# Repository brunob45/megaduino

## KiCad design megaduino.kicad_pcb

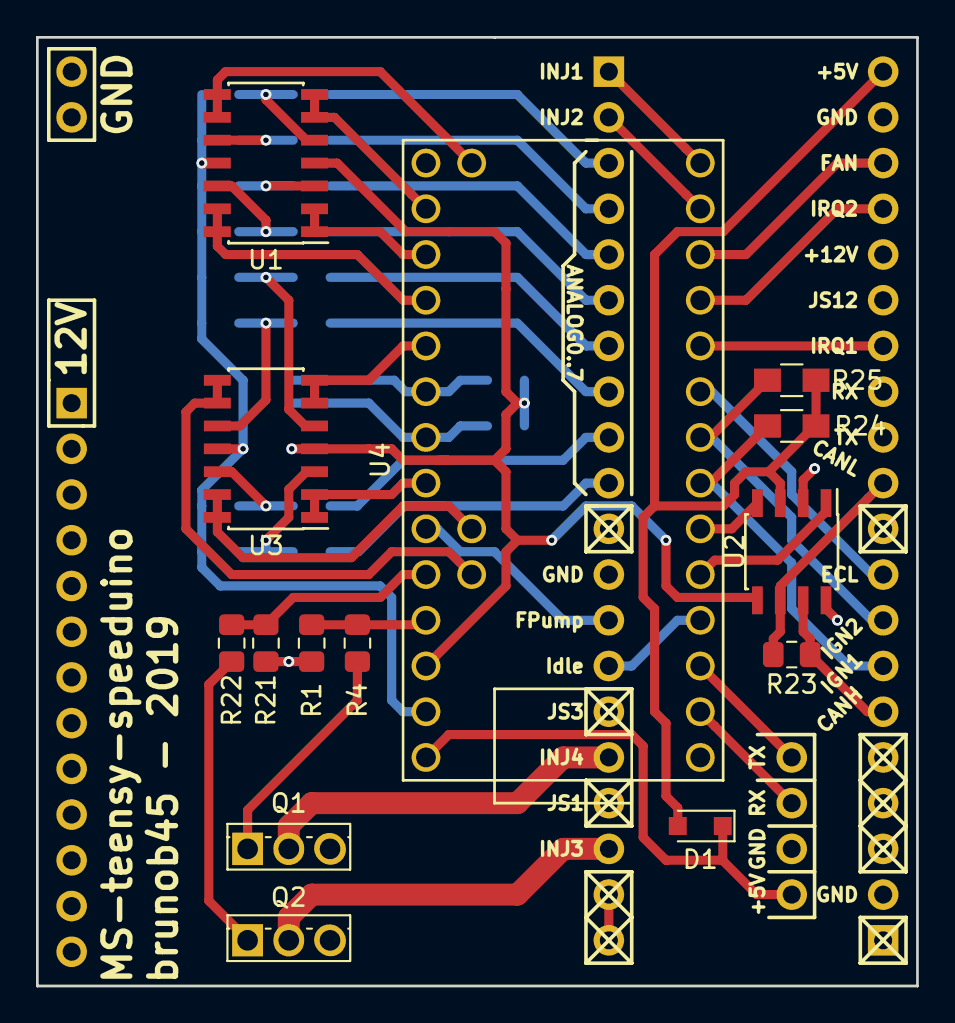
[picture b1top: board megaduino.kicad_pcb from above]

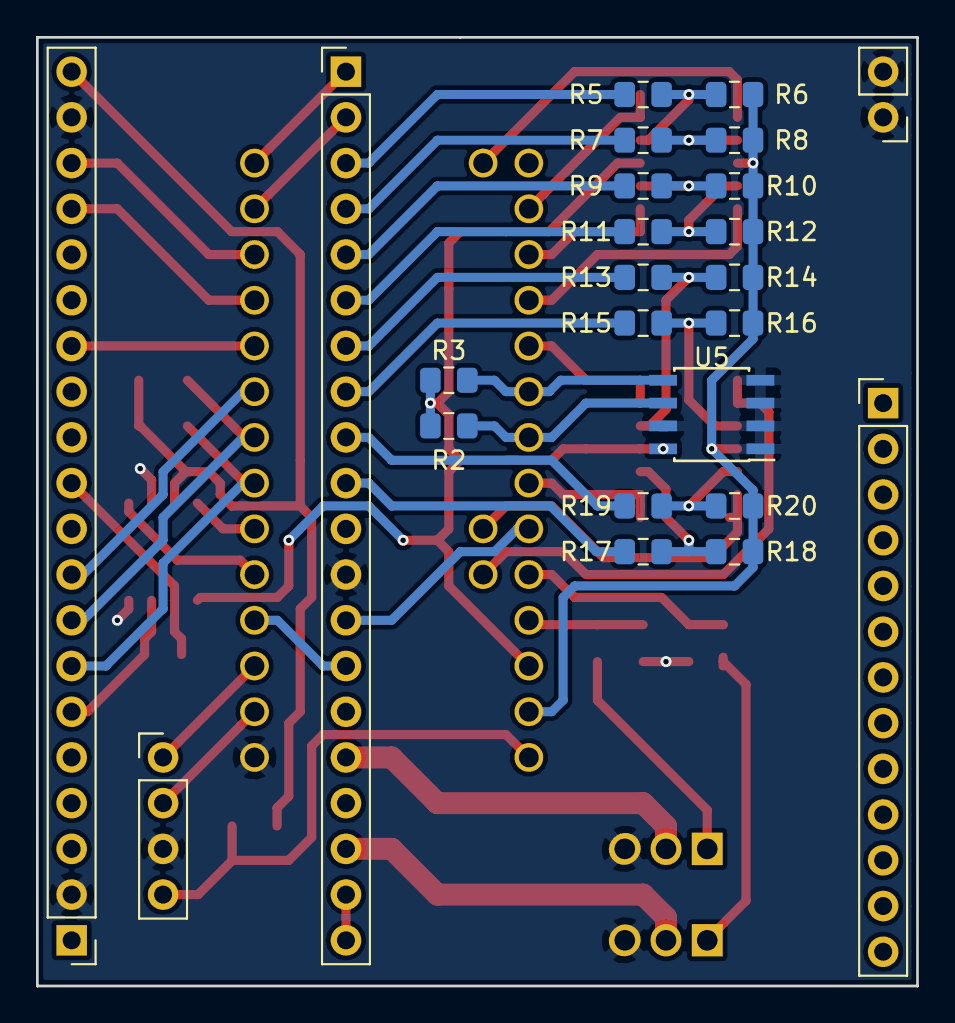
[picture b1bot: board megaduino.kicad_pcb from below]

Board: 2 copper layers, 48.9 x 52.7 mm, 38 parts (24 on the bottom side), 54 nets.

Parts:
D1: D_Schottky; D_SOD-323_HandSoldering
J1, J2: Conn_01x20_Female; Pin_Header_Straight_1x20_Pitch2.54mm
J3: Conn_01x13_Male; PinHeader_1x13_P2.54mm_Vertical
J4: Conn_01x02_Male; PinHeader_1x02_P2.54mm_Vertical
J5: Conn_01x04_Male; PinHeader_1x04_P2.54mm_Vertical
Q1, Q2: RFD14N05L; TO-251-3_Vertical
R1, R6, R8, R10, R12, R14, R16, R18, R20, R21: 91k; R_0805_2012Metric_Pad1.15x1.40mm_HandSolder
R2, R3, R4, R22: 1k; R_0805_2012Metric_Pad1.15x1.40mm_HandSolder
R5, R7, R9, R11, R13, R15, R17, R19: 49k; R_0805_2012Metric_Pad1.15x1.40mm_HandSolder
R23: 120; R_0805_2012Metric_Pad1.15x1.40mm_HandSolder
R24, R25: 1k; R_0805_HandSoldering
U1, U3: LMV324; SOIC-14_3.9x8.7mm_P1.27mm
U2: MCP2562-E-SN; SOIC-8_3.9x4.9mm_P1.27mm
U4: Teensy3.2; Teensy32
U5: AT24CS02-XHM; SOIC-8_3.9x4.9mm_P1.27mm

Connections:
+3V3: R2.1, R3.1, U1.4, U2.5, U3.4, U4.31, U5.8
+5V: D1.2, J1.20, R24.1, R25.1, U2.3
A0: U1.6, U1.7, U4.21
A1: U1.1, U1.2, U4.22
A2: U1.8, U1.9, U4.19
A3: U1.13, U1.14, U4.23
A4: U3.6, U3.7, U4.24
A5: U3.8, U3.9, U4.36
A6: U3.13, U3.14, U4.37
A7: U3.1, U3.2, U4.27
AD0: J2.3, R5.1
AD1: J2.4, R7.1
AD2: J2.5, R9.1
AD3: J2.6, R11.1
AD4: J2.7, R13.1
AD5: J2.8, R15.1
AD6: J2.9, R19.1
AD7: J2.10, R17.1
CANH: J1.6, R23.1, U2.7
CANL: J1.11, R23.2, U2.6
ECL: J1.9, U4.9
Earth: J1.2, J1.19, J2.12, J4.1, J4.2, J5.3, Q1.3, Q2.3, R1.1, R21.1, U2.2, U2.8, U4.1, U5.1, U5.2, U5.3, U5.4, U5.7
FAN: J1.18, U4.12
FP: J2.13, U4.28
GNDA: R6.2, R8.2, R10.2, R12.2, R14.2, R16.2, R18.2, R20.2, U1.11, U3.11, U4.32
IGN1: J1.7, R24.2, U4.7
IGN2: J1.8, R25.2, U4.8
INJ1: J2.1, U4.14
INJ2: J2.2, U4.13
INJ3: R21.2, R22.2, U4.29
INJ4: R1.2, R4.2, U4.30
IRQ0: J1.14, U4.10
IRQ1: J1.17, U4.11
Idle: J2.14, U4.4
JS0: J2.18, Q2.2
JS2: J2.16, Q1.2
unnamed: D1.1, J5.4, U4.33
unnamed: J2.19, J2.20
unnamed: J5.1, U4.3
unnamed: J5.2, U4.2
unnamed: Q1.1, R4.1
unnamed: Q2.1, R22.1
unnamed: R2.2, U4.26, U5.6
unnamed: R3.2, U4.25, U5.5
unnamed: R5.2, R6.1, U1.5
unnamed: R7.2, R8.1, U1.10
unnamed: R9.2, R10.1, U1.3
unnamed: R11.2, R12.1, U1.12
unnamed: R13.2, R14.1, U3.5
unnamed: R15.2, R16.1, U3.10
unnamed: R17.2, R18.1, U3.3
unnamed: R19.2, R20.1, U3.12
unnamed: U2.1, U4.5
unnamed: U2.4, U4.6

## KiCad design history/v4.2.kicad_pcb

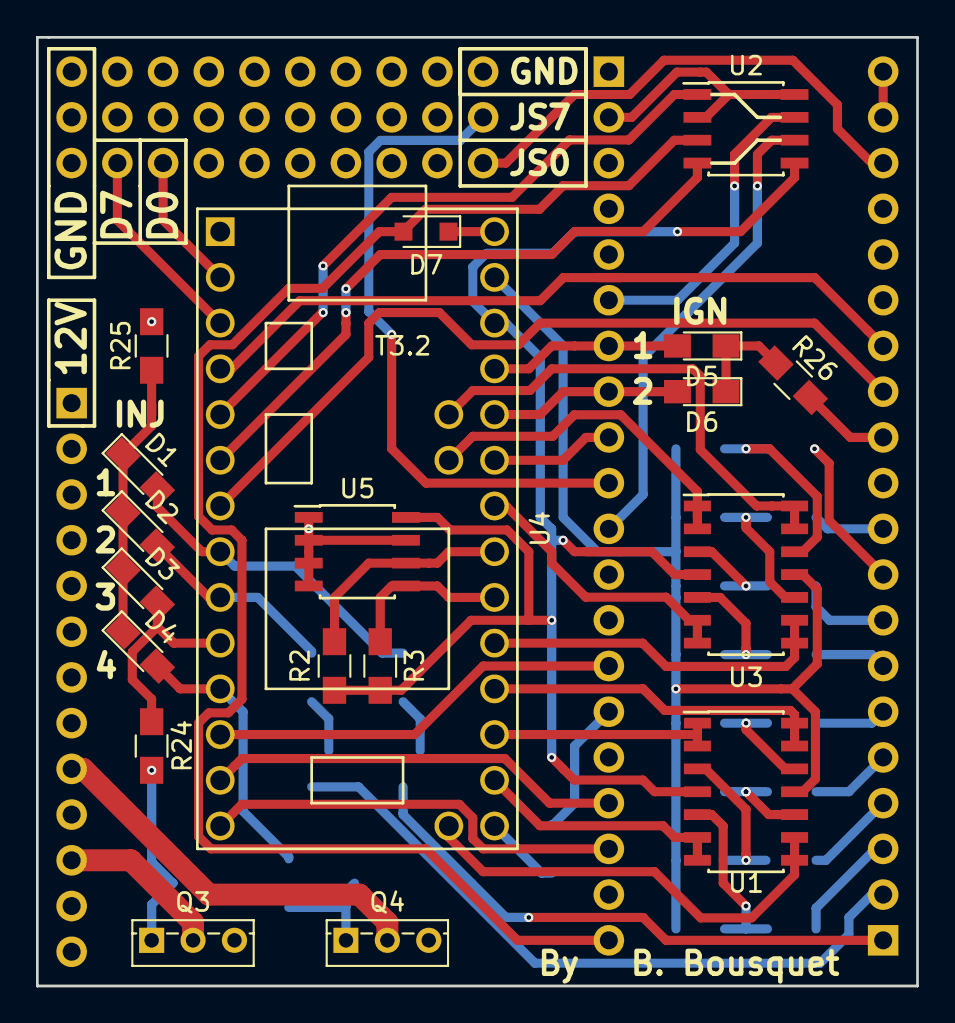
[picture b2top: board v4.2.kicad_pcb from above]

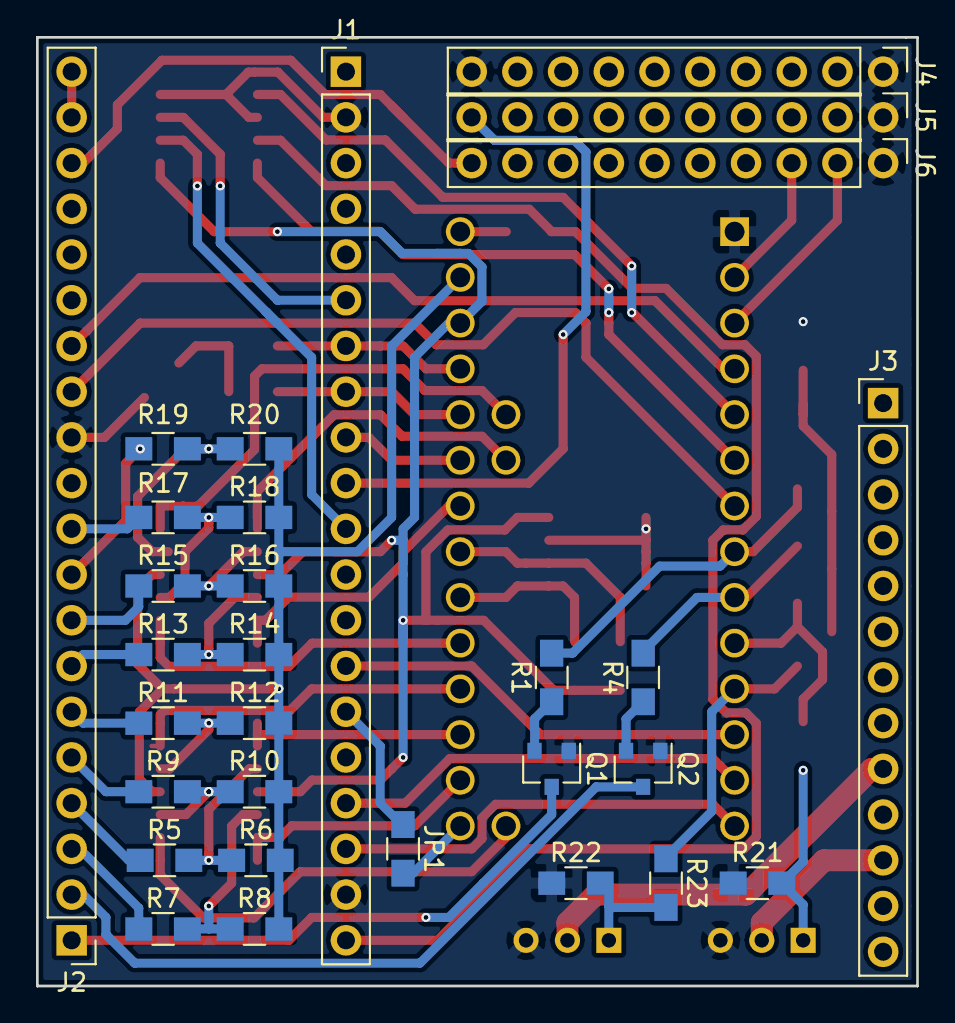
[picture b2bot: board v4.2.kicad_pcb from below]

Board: 2 copper layers, 48.9 x 52.7 mm, 49 parts (30 on the bottom side), 64 nets.

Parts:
D1, D2, D3, D4, D5, D6: LED; LED_0805_HandSoldering
D7: D_Schottky; D_SOD-323_HandSoldering
J1, J2: Conn_01x20_Female; Pin_Header_Straight_1x20_Pitch2.54mm
J3: Conn_01x13_Male; Pin_Header_Straight_1x13_Pitch2.54mm
J4, J5, J6: Conn_01x10_Male; Pin_Header_Straight_1x10_Pitch2.54mm
JP1: Jumper; R_0805_HandSoldering
Q1, Q2: 2N2219; SOT-23
Q3, Q4: Q_NMOS_GDS; TO-251_IPAK_Vertical
R1, R2, R3, R4, R23, R24: 1k; R_0805_HandSoldering
R5, R7, R9, R11, R13, R15, R17, R19: 180k; R_0805_HandSoldering
R6, R8, R10, R12, R14, R16, R18, R20: 330k; R_0805_HandSoldering
R21, R22: 100k; R_0805_HandSoldering
R25, R26: R; R_0805_HandSoldering
U1, U3: LMV324; SOIC-14_3.9x8.7mm_Pitch1.27mm
U2: MCP2562-E/P; SOIC-8_3.9x4.9mm_Pitch1.27mm
U4: Teensy3.2; Teensy32
U5: AT24CS02-XHM; SOIC-8_3.9x4.9mm_Pitch1.27mm

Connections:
+3V3: R2.1, R3.1, U1.4, U2.5, U3.4, U4.31, U5.8
+5V: D7.2, J1.20, U2.3
A0: U1.6, U1.7, U4.21
A1: U1.1, U1.2, U4.22
A2: U1.8, U1.9, U4.19
A3: U1.13, U1.14, U4.23
A4: U3.6, U3.7, U4.27
A5: U3.1, U3.2, U4.37
A6: U3.13, U3.14, U4.36
A7: U3.8, U3.9, U4.24
AD0: J2.3, R7.1
AD1: J2.4, R5.1
AD2: J2.5, R9.1
AD3: J2.6, R11.1
AD4: J2.7, R13.1
AD5: J2.8, R15.1
AD6: J2.9, R19.1
AD7: J2.10, R17.1
CANH: J1.6, U2.7
CANL: J1.11, U2.6
D0: J6.3, U4.2
D7: J6.2, U4.3
ECL: J1.9, U4.28
Earth: J1.2, J1.19, J2.12, J4.1, J4.10, J5.1, J6.1, Q1.1, Q2.1, Q3.3, Q4.3, R21.1, R22.1, R25.2, R26.2, U2.2, U2.8, U4.1, U5.1, U5.2, U5.3, U5.4, U5.7
FAN: J1.18, U4.14
FP: J2.13, U4.7
GNDA: R6.2, R8.2, R10.2, R12.2, R14.2, R16.2, R18.2, R20.2, U1.11, U3.11, U4.32
IGN1: D5.2, J1.7, U4.30
IGN2: D6.2, J1.8, U4.29
INJ1: D1.2, R1.2, U4.8
INJ2: D2.2, R4.2, U4.9
INJ3: D3.2, R24.1, U4.10
INJ4: D4.2, R23.1, U4.11
IRQ0: J1.14, U4.12
IRQ1: J1.17, U4.13
Idle: J2.14, U4.4
JS0: J2.18, J6.10
JS7: J1.10, J5.10
JS12: J1.15, JP1.1
unnamed: D1.1, D2.1, D3.1, D4.1, R25.1
unnamed: D5.1, D6.1, R26.1
unnamed: D7.1, U4.33
unnamed: J2.1, Q1.3
unnamed: J2.2, Q2.3
unnamed: J2.19, J2.20
unnamed: J3.9, Q4.2
unnamed: J3.11, Q3.2
unnamed: JP1.2, U4.20
unnamed: Q1.2, R1.1
unnamed: Q2.2, R4.1
unnamed: Q3.1, R21.2, R24.2
unnamed: Q4.1, R22.2, R23.2
unnamed: R2.2, U4.26, U5.6
unnamed: R3.2, U4.25, U5.5
unnamed: R5.2, R6.1, U1.3
unnamed: R7.2, R8.1, U1.5
unnamed: R9.2, R10.1, U1.10
unnamed: R11.2, R12.1, U1.12
unnamed: R13.2, R14.1, U3.5
unnamed: R15.2, R16.1, U3.3
unnamed: R17.2, R18.1, U3.10
unnamed: R19.2, R20.1, U3.12
unnamed: U2.1, U4.5
unnamed: U2.4, U4.6

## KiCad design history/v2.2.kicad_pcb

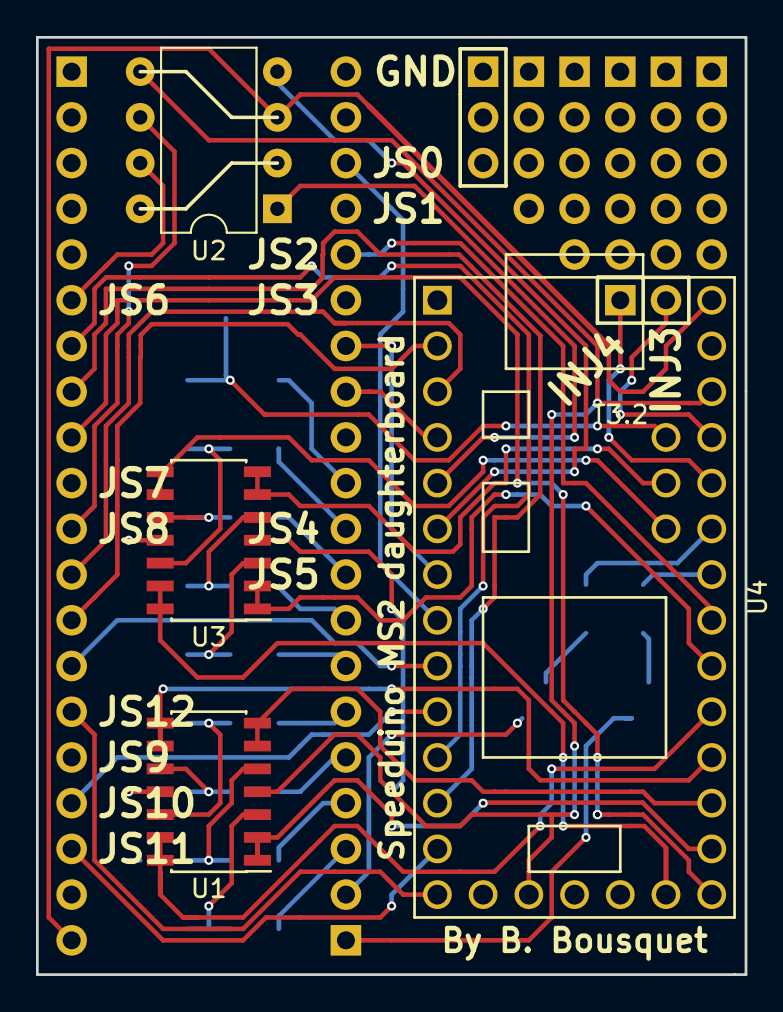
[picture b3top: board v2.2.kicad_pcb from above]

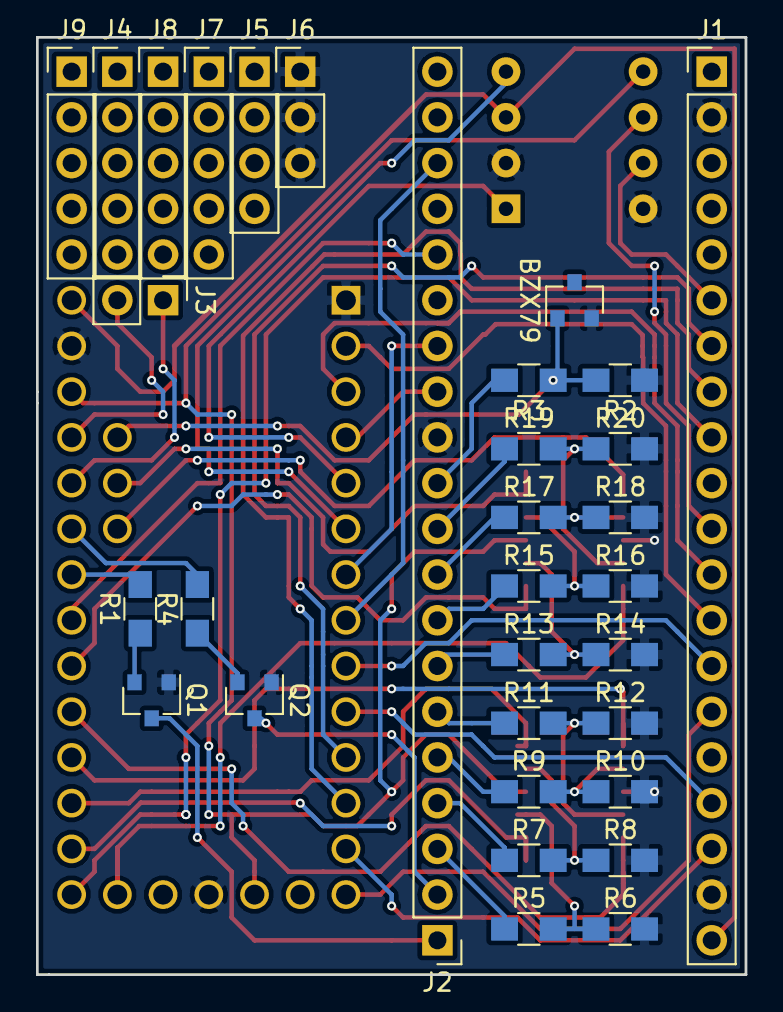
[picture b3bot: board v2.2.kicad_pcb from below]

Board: 2 copper layers, 39.4 x 52.1 mm, 36 parts (32 on the bottom side), 54 nets.

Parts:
BZX79: D_Zener; SOT-23
J1, J2: Conn_01x20_Female; Pin_Header_Straight_1x20_Pitch2.54mm
J3: Conn_01x02_Female; Pin_Header_Straight_1x02_Pitch2.54mm
J4, J7, J8, J9: Conn_01x05_Male; Pin_Header_Straight_1x05_Pitch2.54mm
J5: Conn_01x04_Male; Pin_Header_Straight_1x04_Pitch2.54mm
J6: Conn_01x03_Male; Pin_Header_Straight_1x03_Pitch2.54mm
Q1, Q2: 2N2219; SOT-23
R1, R4: 1k; R_0805_HandSoldering
R2, R6, R8, R10, R12, R14, R16, R18, R20: 330k; R_0805_HandSoldering
R3, R5, R7, R9, R11, R13, R15, R17, R19: 180k; R_0805_HandSoldering
U1, U3: LMV324; SOIC-14_3.9x8.7mm_Pitch1.27mm
U2: MCP2562-E/P; DIP-8_W7.62mm
U4: Teensy3.2; Teensy32

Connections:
+3.3VA: BZX79.1, R2.2, R3.1, U4.35
+3V3: U1.4, U2.5, U3.4, U4.16, U4.31
+5V: J1.20, U2.3, U4.33
A0: U1.1, U1.2, U4.21
A1: U1.6, U1.7, U4.22
A2: U1.8, U1.9, U4.23
A3: U1.13, U1.14, U4.24
A4: U3.1, U3.2, U4.25
A5: U3.6, U3.7, U4.36
A6: U3.8, U3.9, U4.37
A7: U3.13, U3.14, U4.19
AD0: J2.3, R5.1
AD1: J2.4, R7.1
AD2: J2.5, R9.1
AD3: J2.6, R11.1
AD4: J2.7, R13.1
AD5: J2.8, R15.1
AD6: J2.9, R17.1
AD7: J2.10, R19.1
CANH: J1.6, U2.7
CANL: J1.11, U2.6
ECL: J1.9, U4.20
Earth: BZX79.2, J1.2, J1.19, J2.12, J6.1, J6.2, J6.3, Q1.1, Q2.1, R2.1, R6.2, R8.2, R10.2, R12.2, R14.2, R16.2, R18.2, R20.2, U1.11, U2.2, U2.8, U3.11, U4.1, U4.17, U4.32
FP: J2.13, U4.4
IGN1: J1.7, U4.11
IGN2: J1.8, U4.12
INJ1: R1.2, U4.27
INJ2: R4.2, U4.28
INJ3: J3.1, U4.29
INJ4: J3.2, U4.30
IRQ0: J1.14, U4.9
IRQ1: J1.17, U4.10
Idle: J2.14, U4.7
JS0: J2.18, U4.8
JS2: J2.16, U4.26
JS11: J1.18, U4.13
JS12: J1.15, U4.14
unnamed: J2.1, Q1.3
unnamed: J2.2, Q2.3
unnamed: J2.11, R3.2
unnamed: Q1.2, R1.1
unnamed: Q2.2, R4.1
unnamed: R5.2, R6.1, U1.3
unnamed: R7.2, R8.1, U1.5
unnamed: R9.2, R10.1, U1.10
unnamed: R11.2, R12.1, U1.12
unnamed: R13.2, R14.1, U3.3
unnamed: R15.2, R16.1, U3.5
unnamed: R17.2, R18.1, U3.10
unnamed: R19.2, R20.1, U3.12
unnamed: U2.1, U4.5
unnamed: U2.4, U4.6
RX: J1.13, U4.2
TX: J1.12, U4.3

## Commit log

2018-11-15 Add project files
2018-11-28 updated to kicad 5.0.1 and redo all over again
2018-11-28 add board picture
2018-11-28 image was too large
2018-12-05 version pas mal finale
2018-12-06 js7 in now on proto area
2018-12-06 move misc files to docs folder
2018-12-06 move pcb history files to history folder
2018-12-16 remove components from under teensy
2018-12-16 add inj3-4 drivers and CAN transceiver - no proto (yet?)
2018-12-17 add 120R resistor for CAN
2019-01-24 add Serial-BT HC-06 connection
2019-02-26 the HC connector was 180 deg; begin corrections
2019-03-01 reverse HC connector pt2
2019-03-01 reverse HC connector pt3
2019-03-01 reverse HC connector done
2019-03-02 minor changes
2019-03-04 add proto area
2019-03-04 final version 2.1
2019-03-28 add pull-up resistors on injector outputs
2019-03-28 pull-up on ignition and move IGN3-4 transistors away from usb connector
